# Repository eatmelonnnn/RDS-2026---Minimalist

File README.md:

# Minimalist Finger

## Assembly Instructions

### 1. Finger Assembly

1. Put bearings into flexion pulleys (3x).
   > 
2. Put bearings and pulleys onto bearing pins (2x).
   > 
   > 
3. Tie slipknots onto spring/tendon pins (2x).
4. Snap spring/tendon pin into fingertip and pull tendon into groove.
   > 
5. Snap bearing pin into place.
   > 
6. Snap middle linkage onto bearing pin.
   > 
7. Route tendon through and pull into groove.
   > 
8. Snap second tendon pin on and pull tendon into groove.
   > 
9. Snap second bearing pin into middle link.
   > 
10. Snap knuckle onto bearing pin.
    > 
11. Thread tendons through knuckle and onto grooves.
    > 
12. Put bearings into splay pulleys (2x).
    > 
13. Put belt pulley onto shaft.
    > 
14. Align all splay components and push shaft through.
    > 
15. Wrap tendons around splay pulleys and thread through base.
    > 
16. Put springs onto pins and snap onto linkages (x2).
    > 
17. Gently pry up tendon/spring pins and loop springs on (x2).
    > 

---

##3 2. Mounting Assembly

1. Assemble main 80-20 frame with plates and bolts.
   > 
2. Put vertical 80-20 on with brackets and bolts.
   > 
3. Put pulley on splay motor.
   > 
4. Put splay motor on splay plate.
   > 
5. Put tensioner on splay plate.
   > 
6. Put splay plate on vertical 80-20 with brackets and bolts.
   > 
7. Put finger plate on vertical 80-20 with bolts.
   > 
8. Put tension plates on 80-20 with bolts (2x).
   > 
9. Put motor plates on 80-20 with bolts (2x).
   > 
10. Put pulleys on flexion motors (2x).
    > 
11. Put tension sensors on tension plates (2x).
    > 
12. Put motors on motor plates (2x).
    > 

---

### 3. Finger/Mounting Integration Assembly

1. Bolt finger onto plate and put splay belt on.
   > 
2. Tension splay belt with allen key.
   > 
3. Thread tendon from finger through tension sensor and onto pulley.
   > 
4. Terminate tendon on motor pulley with slipknot and screw.

---
## Instructions to Run Finger Program/Operate Finger Once Assembled

1. Locate main folder in the Electrical and upload `main.ino` to the Teensy 4.1.

2. Let calibration sequence run without interference.

3. Choose desired behavior/test.
   - For all states except the flexion-extension test, simply press the specified button to trigger the state switch.
   - You can switch between any two states by pressing the corresponding buttons.
   - For the MCP flexion-extension test:
     - Move the jumper wire on Pin 33 from **GND** to **3.3V**.
     - This will trigger the flexion-extension test.
     - At this point, there is no way to return to the other states without rerunning the program from the start on the Teensy.

4. When finished, press the **E-stop** to turn off the motors.

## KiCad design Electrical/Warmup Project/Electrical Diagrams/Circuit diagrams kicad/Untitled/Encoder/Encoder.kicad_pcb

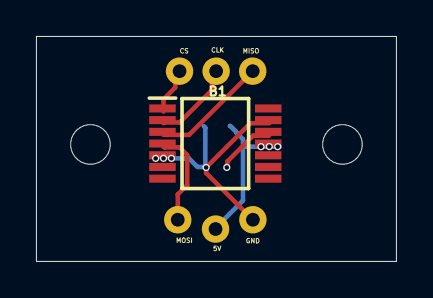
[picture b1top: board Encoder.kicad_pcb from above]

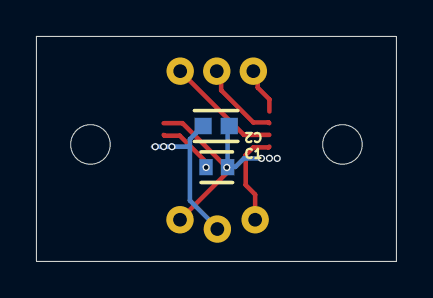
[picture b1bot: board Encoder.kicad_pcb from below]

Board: 2 copper layers, 20.0 x 12.5 mm, 3 parts (2 on the bottom side), 3 nets.

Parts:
B1: AS5147U-HTSM; SOP65P640X120-14N
C1: 100nF; FP-C0603C-CF-MFG
C2: 1uF; FP-GRT188-0_1-e0_2_0_5-IPC_B

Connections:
+5: B1.11, C2.1
GND: B1.5, B1.13, C1.2, C2.2
NetB1_12: B1.12, C1.1

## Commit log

2026-01-29 Control block diagrams 1/28
2026-01-30 moved electrical stuff into electrical folder and created mechanical folder
2026-01-30 Added linkage diff CAD
2026-01-30 impedance control added
2026-01-30 minor change to fix typo
2026-01-30 added INA125
2026-01-30 exploded cbd before peer review
2026-01-31 test
2026-01-31 adding in specific component names
2026-01-31 a little more in depth
2026-01-31 Ki Cad Files
2026-01-31 final cbd
2026-01-31 checkpoint 1 submission added
2026-02-02 Corrections
2026-02-06 Direct drive 02/06
2026-02-08 Updates 2/7
2026-02-14 Motor attachment
2026-02-14 motor
2026-02-16 Reorganized
2026-02-16 final control block diagram
2026-02-16 added motor shaft clamp
2026-02-16 updated clamp assembly and clamp to ensure that the tolerances where right
2026-02-16 Adding encoder reading and cyclic messaging
2026-02-26 a lot of stuff lol
2026-03-03 On axis tendon routing finger link CAD draft
2026-03-05 Last iteration with vgrooves in center
2026-03-05 Printed version 1
2026-03-05 Created MCP
2026-03-05 Changed MCP
2026-03-06 Kinematics
2026-03-10 finger and motor supports
2026-03-10 Static DIP and updated pulley radius
2026-03-10 New parts for splay
2026-03-10 Prefinalized MCP
2026-03-10 3/10
2026-03-10 Updated snap fit pin retention and pulley sizing
2026-03-10 Added motors
2026-03-10 Another MCP Revision
2026-03-10 Add .gitignore to block SolidWorks temp and backup files
2026-03-10 Updated code
2026-03-10 load cell assembly and splay mount assembly
2026-03-11 Progress on tension mount
2026-03-11 What's going on?
2026-03-11 Finished tension sensor
2026-03-11 3/11
2026-03-11 Static DIP for second phalange
2026-03-11 Minor MCP updates
2026-03-11 Reworked splay spacers
2026-03-11 Revised MCP
2026-03-11 Base hole changes
2026-03-11 checkpoint
2026-03-11 Tendon route slot and MCP flex hardstop
2026-03-11 new splay design
2026-03-11 Modeled tendons
2026-03-11 in progress
2026-03-11 closer to finishing
2026-03-11 Tendon routing
2026-03-12 Idek what's broken
2026-03-12 intermediate push
2026-03-12 adfadfadf
2026-03-12 New bolts
2026-03-12 More bolts
2026-03-13 Base plate
2026-03-13 redesigned splay mount for new gearbox and for metric screws
2026-03-13 3/13
2026-03-13 4:43
2026-03-13 6:43
2026-03-14 9:05
2026-03-14 fix weird mating
2026-03-14 fix screws
2026-04-01 stls
2026-04-02 removed parallel tensioning and replaced with idler pulley
2026-04-03 Redesigned mounting
2026-04-03 sdf files for reduced assembly
2026-04-03 Moved Kinematics Folder
2026-04-03 Changed name for Motor Mounts
2026-04-04 Working now?
2026-04-04 Fixed the fire
2026-04-06 Drake
2026-04-08 main links mass overwrite in solidworks
2026-04-08 Edited materials
2026-04-08 Finger look like finger
2026-04-08 Flipped pulley
2026-04-08 bearing material change
2026-04-09 assembly reset
2026-04-09 changing bearing and timing pulley materials
2026-04-10 Updated Tendon width and MCP clearance
2026-04-10 temp
2026-04-10 New mounting
2026-04-10 fixed dangling parts
2026-04-10 4/10
2026-04-11 full assembly
2026-04-11 setup instructions
2026-04-17 Tension sensing and motor mount manufacturability
2026-04-17 Updated Schematics
2026-04-17 Updated Circuit Diagrams
2026-04-17 fixed tendon sensor heights
2026-04-17 added tension sensor mount holes
2026-04-17 Hopefully working?
2026-04-17 Redesigned mount, surely for the last time
2026-04-17 Electrical setup
2026-04-17 Electrical platform
2026-04-17 plate mount holes
2026-04-21 Updated finger mounting
2026-04-21 Figured out new motor pulleys - potentially deleted Josh's work
2026-04-21 Changed the pulley
2026-04-21 Tweaked mounting panels
2026-04-21 Fixed stuff
2026-04-21 new electronics platform for cubemars motors
2026-04-22 Finger spring mounting changes
2026-04-22 Final design
2026-04-23 CubeMars Splay Mount
2026-04-24 Updated Sensor Code
2026-05-01 Reconfigured wrap-around
2026-05-01 Progress
2026-05-01 Stuff
2026-05-02 pcb updates
2026-05-02 Finished some finger changes
2026-05-03 Create Power demo
2026-05-03 straggler updates
2026-05-04 Splay hardstop change
2026-05-04 calibration addition
2026-05-04 calibration compiles
2026-05-04 working calibration (ish)
2026-05-04 Changed motor pulleys
2026-05-04 Pin distance update
2026-05-05 added step response and fake calibration
2026-05-05 Pin movement new hardstop
2026-05-05 Added grooves, and new closed MCP splay base. Also changed termination style on pulley.
2026-05-05 Changed the motor pulley a bit
2026-05-05 Random stuff idk
2026-05-06 calibration values
2026-05-06 power demo mostly done
2026-05-06 Schematic Updates
2026-05-08 Finished adding mounts
2026-05-10 starting force sensor
2026-05-10 Ignore .history directories
2026-05-10 Fix .history ignore rule
2026-05-18 simulation
2026-05-18 3DP splay and flex mounts
2026-05-18 Splay rework to re add snap fit
2026-05-20 more code changes for force control
2026-05-20 force fixes and starting kinematics
2026-05-20 further force prints
2026-05-20 simulation updates 5/20
2026-05-20 Finished kinematics code
2026-05-21 Updated PCB
2026-05-21 Revert "Merge branch 'main' of https://github.com/eatmelonnnn/RDS-2026---Minimalist"
    This reverts commit 883e1484304e175d3b4adfd648e5949d44f51669, reversing
    changes made to a4f640ebd322d30c9f0196dbf41a23721d0c68da.
2026-05-21 Reapply "Merge branch 'main' of https://github.com/eatmelonnnn/RDS-2026---Minimalist"
    This reverts commit 2f54a51d8f4bcf68ea62a4f5b891c3c471be51b2.
2026-05-21 Fixing messed up merge
2026-05-22 ellipse tracking and fingertip force control
2026-05-25 simulation updates
2026-05-29 lots of stuff
2026-05-31 state machine
2026-05-31 state machine first implementation
2026-06-02 state machine tweaks
2026-06-02 electrical mounts
2026-06-03 feedforward torque in splay
2026-06-04 final before massive force changes
2026-06-05 simulation final updates
2026-06-05 more work
2026-06-09 small changes
2026-06-10 flexion extension data
2026-06-10 README with assembly instructions made
2026-06-10 clean up electrical folder
2026-06-11 readme file update
    Add README for Finger Flick MuJoCo simulation
2026-06-11 simulation readme
2026-06-12 Add step
